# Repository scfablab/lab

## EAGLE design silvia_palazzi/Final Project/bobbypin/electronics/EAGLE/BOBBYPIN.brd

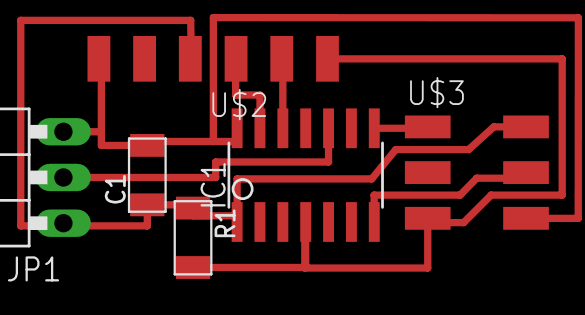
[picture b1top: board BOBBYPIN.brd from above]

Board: 2 copper layers, 6 parts (0 on the bottom side), 9 nets.

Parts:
C1: C1206FAB
IC1: ATTINY44-SSU; SOIC14
JP1: 1X03/90
R1: R1206FAB
U$2: FTDI-SMD-HEADER; 1X06SMD
U$3: AVRISPSMD; 2X03SMD

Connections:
unnamed: IC1.8, U$3.1
unnamed: IC1.7, U$3.4
unnamed: IC1.4, R1.2, U$2.6, U$3.5
unnamed: IC1.9, U$3.3
unnamed: C1.2, IC1.14, JP1.3, U$2.1, U$3.6
unnamed: C1.1, IC1.1, JP1.1, R1.1, U$2.3, U$3.2
unnamed: IC1.13, U$2.4
unnamed: IC1.12, U$2.5
unnamed: IC1.10, JP1.2

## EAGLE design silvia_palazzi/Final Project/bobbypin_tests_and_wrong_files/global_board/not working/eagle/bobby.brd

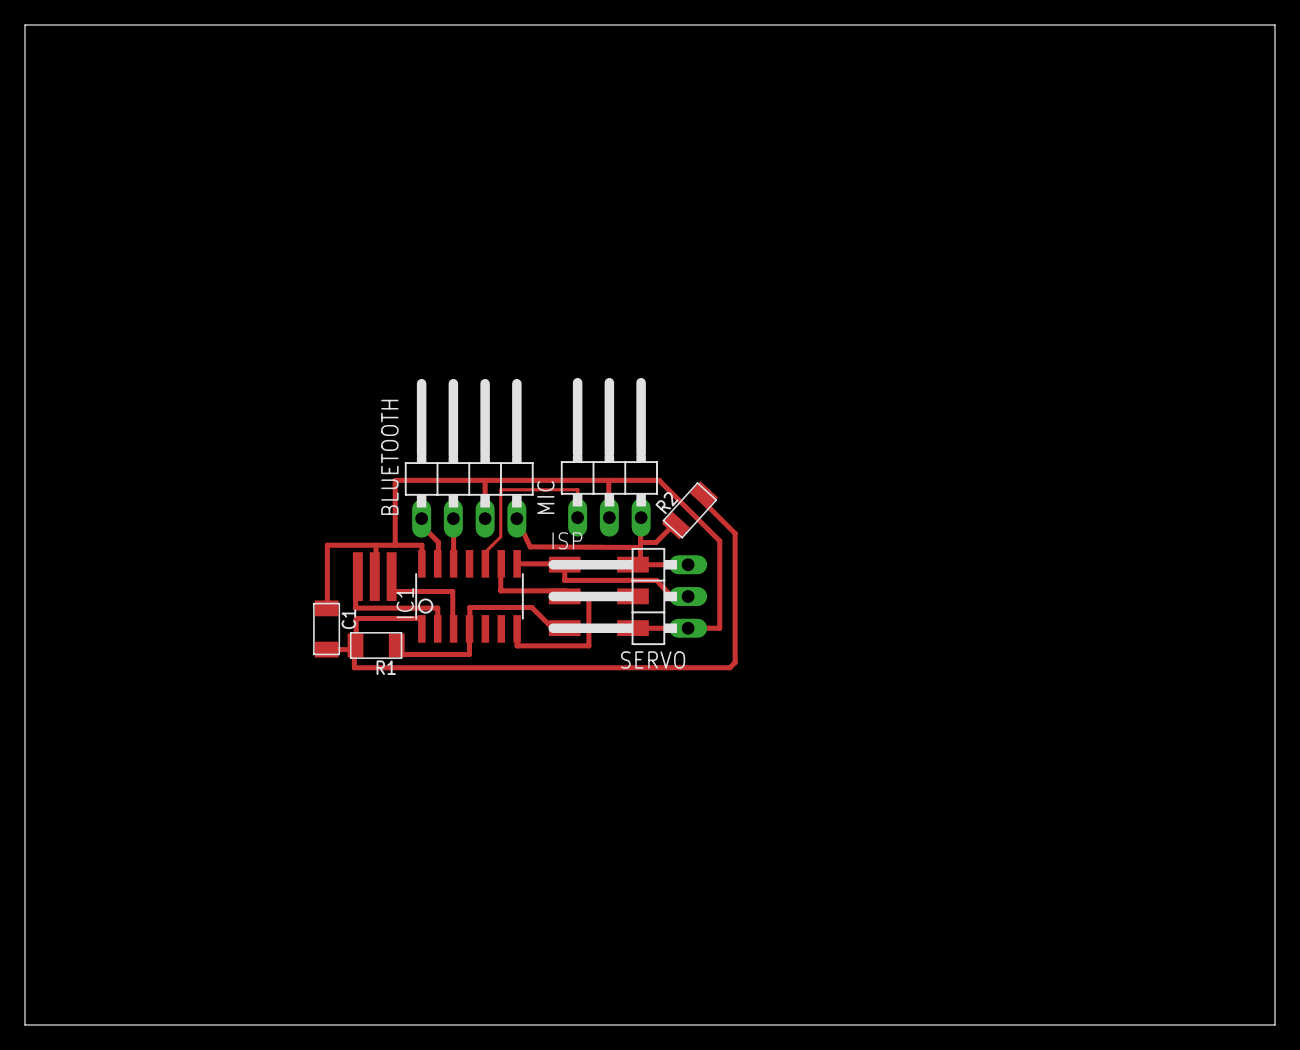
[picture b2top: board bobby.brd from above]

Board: 2 copper layers, 100.0 x 80.0 mm, 9 parts (0 on the bottom side), 11 nets.

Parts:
20MHZ: RESONATOR; EFOBM
BLUETOOTH: 1X04/90
C1: C1206FAB
IC1: ATTINY44-SSU; SOIC14
ISP: AVRISPSMD; 2X03SMD
MIC: 1X03/90
R1, R2: R1206FAB
SERVO: 1X03/90

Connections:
2: 20MHZ.1, IC1.2
3: 20MHZ.3, IC1.3
GND: 20MHZ.2, BLUETOOTH.3, C1.1, IC1.14, ISP.6, MIC.2, SERVO.1
MIC: IC1.10, MIC.1
MISO: IC1.8, ISP.1, SERVO.2
MOSI: IC1.7, ISP.4
RST: IC1.4, ISP.5, R1.1
RX: BLUETOOTH.1, IC1.13
SCK: IC1.9, ISP.3
TX: BLUETOOTH.2, IC1.12
VCC: BLUETOOTH.4, C1.2, IC1.1, ISP.2, MIC.3, R1.2, R2.1, R2.2, SERVO.3

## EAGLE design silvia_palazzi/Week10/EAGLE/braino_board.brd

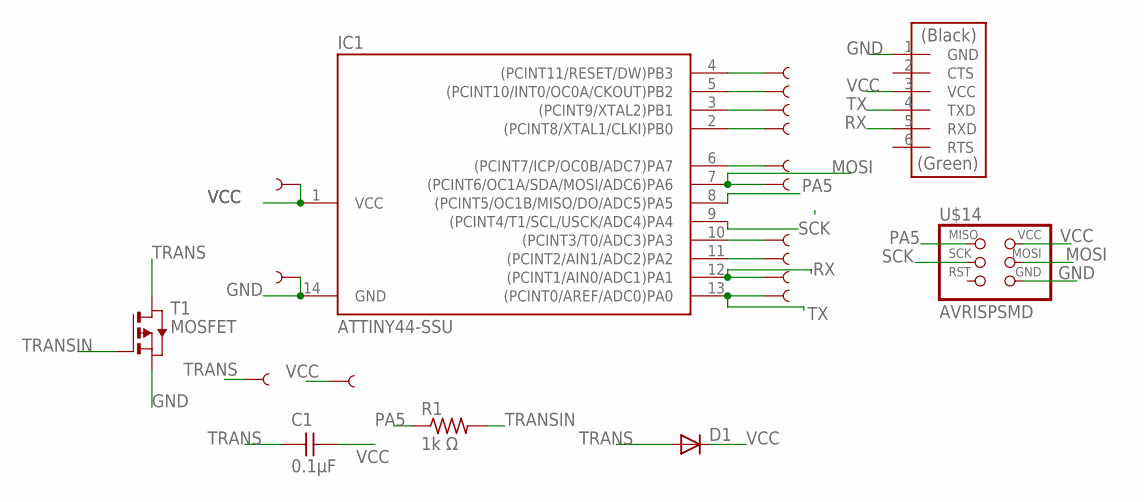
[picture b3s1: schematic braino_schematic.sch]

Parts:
C1: 0.1µF; C1206FAB
D1: DIODESOD123; SOD123
IC1: ATTINY44-SSU; SOIC14
R1: 1k Ω; R1206FAB
T1: MOSFET; SOT-23
U$1, U$2, U$3, U$4, U$5, U$6, U$9, U$10, U$11, U$12, U$15, U$16: SEWTAP10; PETAL-LONG-2-2SIDE
U$13: FTDI-SMD-HEADER; 1X06SMD
U$14: AVRISPSMD; 2X03SMD
U$17, U$18: SEWTAP11; PETAL-TINY

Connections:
GND: IC1.14 (GND), T1.2 (S), U$13.1 (GND), U$14.6 (GND), U$15.1
MOSI: IC1.7 ((PCINT6/OC1A/SDA/MOSI/ADC6)PA6), U$6.1, U$14.4 (MOSI)
unnamed: IC1.4 ((PCINT11/RESET/DW)PB3), U$1.1
unnamed: IC1.5 ((PCINT10/INT0/OC0A/CKOUT)PB2), U$2.1
unnamed: IC1.3 ((PCINT9/XTAL2)PB1), U$3.1
unnamed: IC1.2 ((PCINT8/XTAL1/CLKI)PB0), U$4.1
unnamed: IC1.6 ((PCINT7/ICP/OC0B/ADC7)PA7), U$5.1
unnamed: IC1.10 ((PCINT3/T0/ADC3)PA3), U$9.1
unnamed: IC1.11 ((PCINT2/AIN1/ADC2)PA2), U$10.1
PA5: IC1.8 ((PCINT5/OC1B/MISO/DO/ADC5)PA5), R1.1, U$14.1 (MISO)
RX: IC1.12 ((PCINT1/AIN0/ADC1)PA1), U$11.1, U$13.5 (RXD)
SCK: IC1.9 ((PCINT4/T1/SCL/USCK/ADC4)PA4), U$14.3 (SCK)
TRANS: C1.1, D1.ANODE (A), T1.1 (D), U$18.1
TRANSIN: R1.2, T1.3 (G)
TX: IC1.13 ((PCINT0/AREF/ADC0)PA0), U$12.1, U$13.4 (TXD)
VCC: C1.2, D1.CATHODE (C), IC1.1 (VCC), U$13.3 (VCC), U$14.2 (VCC), U$16.1, U$17.1

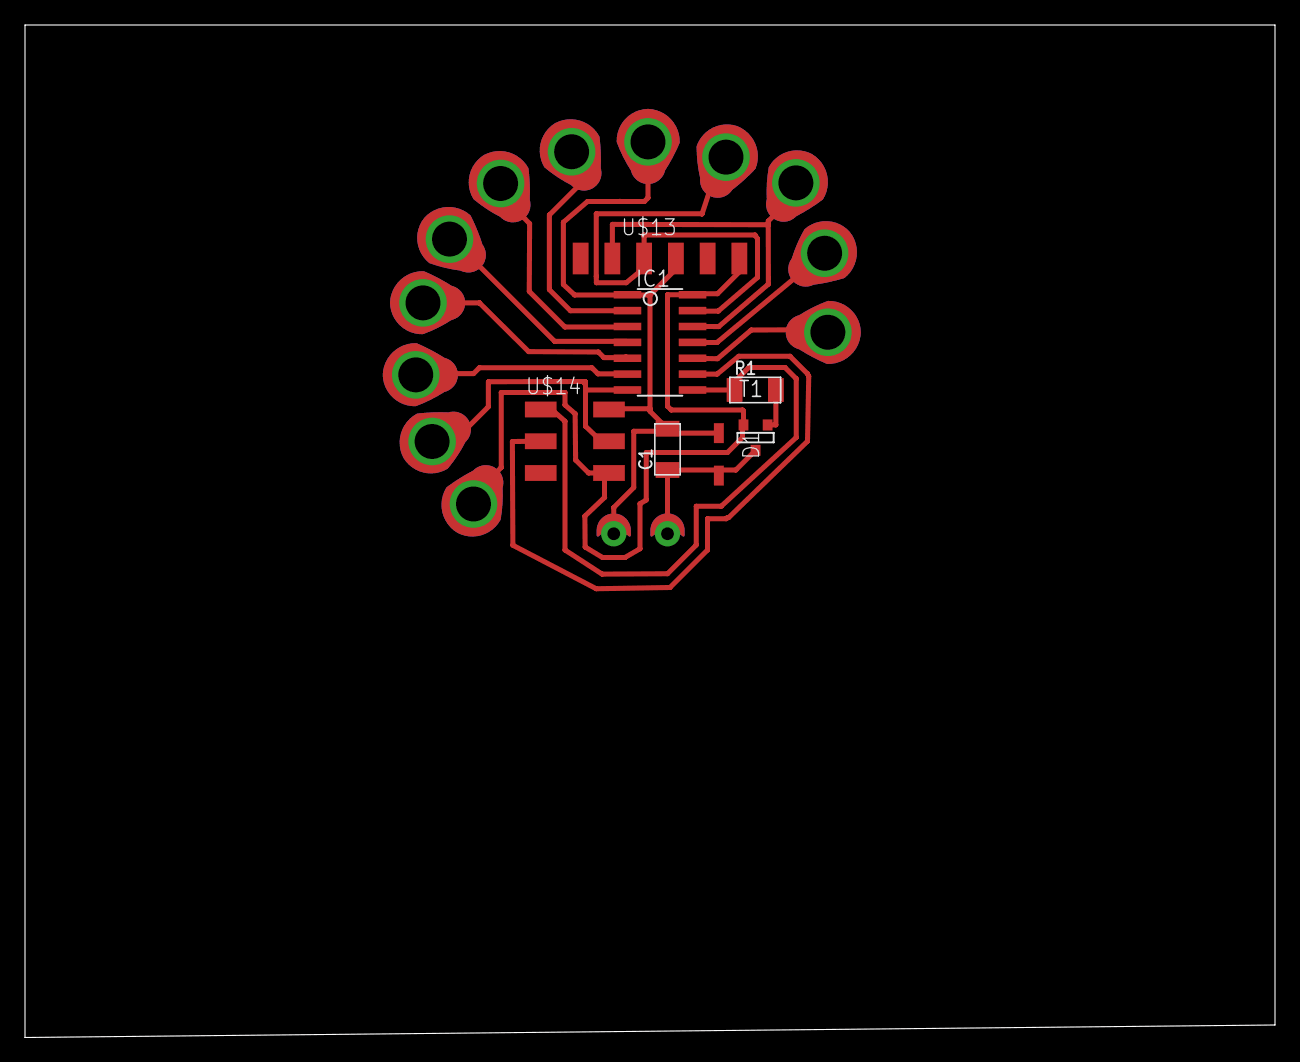
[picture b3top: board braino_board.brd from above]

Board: 2 copper layers, 100.0 x 81.0 mm, 21 parts (0 on the bottom side), 16 nets.
